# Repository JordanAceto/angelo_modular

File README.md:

## Custom 5u format modular synth with 12 modules

### Contains:
- VCO with 5-pulser waveshaper
- VCO with two sub-oscillators
- VCO with LFO range switch
- Voltage controlled wavefolder plus ring-modulator
- Voltage controlled filter with swapable filter-core plug-in boards
- Dual late MS20 style voltage controlled filter
- MIDI to CV plus audio input processor
- Dual 3-input DC coupled mixer
- Modulation source with voltage controlled LFO, sample-and-hold, and white noise source
- Dual Serge style slope generator
- Dual ADSR
- Dual VCA
- +/- 12 volt power supply

### User manuals can be found in the `/user_manuals/` directory. This directory also contains a document outlining any pcb kludges or changes to the current system.

### Documentation for the pcbs is in the `/pcb_docs/` directory

#### Documentation for each pcb consists of the following:
- A very brief README outlining the basics of the pcb

- `/construction_docs/` subdirectory which contains:
  - Gerbers for the circuit board
  - An interactive BOM which can be opened in a web browser
  - A pdf schematic

- `/kicad_docs/` subdirectory which contains the files needed to edit the schematic and pcb layout with kicad

- `/pics/` subdirectory which contains a few rendered pictures of the pcb for reference

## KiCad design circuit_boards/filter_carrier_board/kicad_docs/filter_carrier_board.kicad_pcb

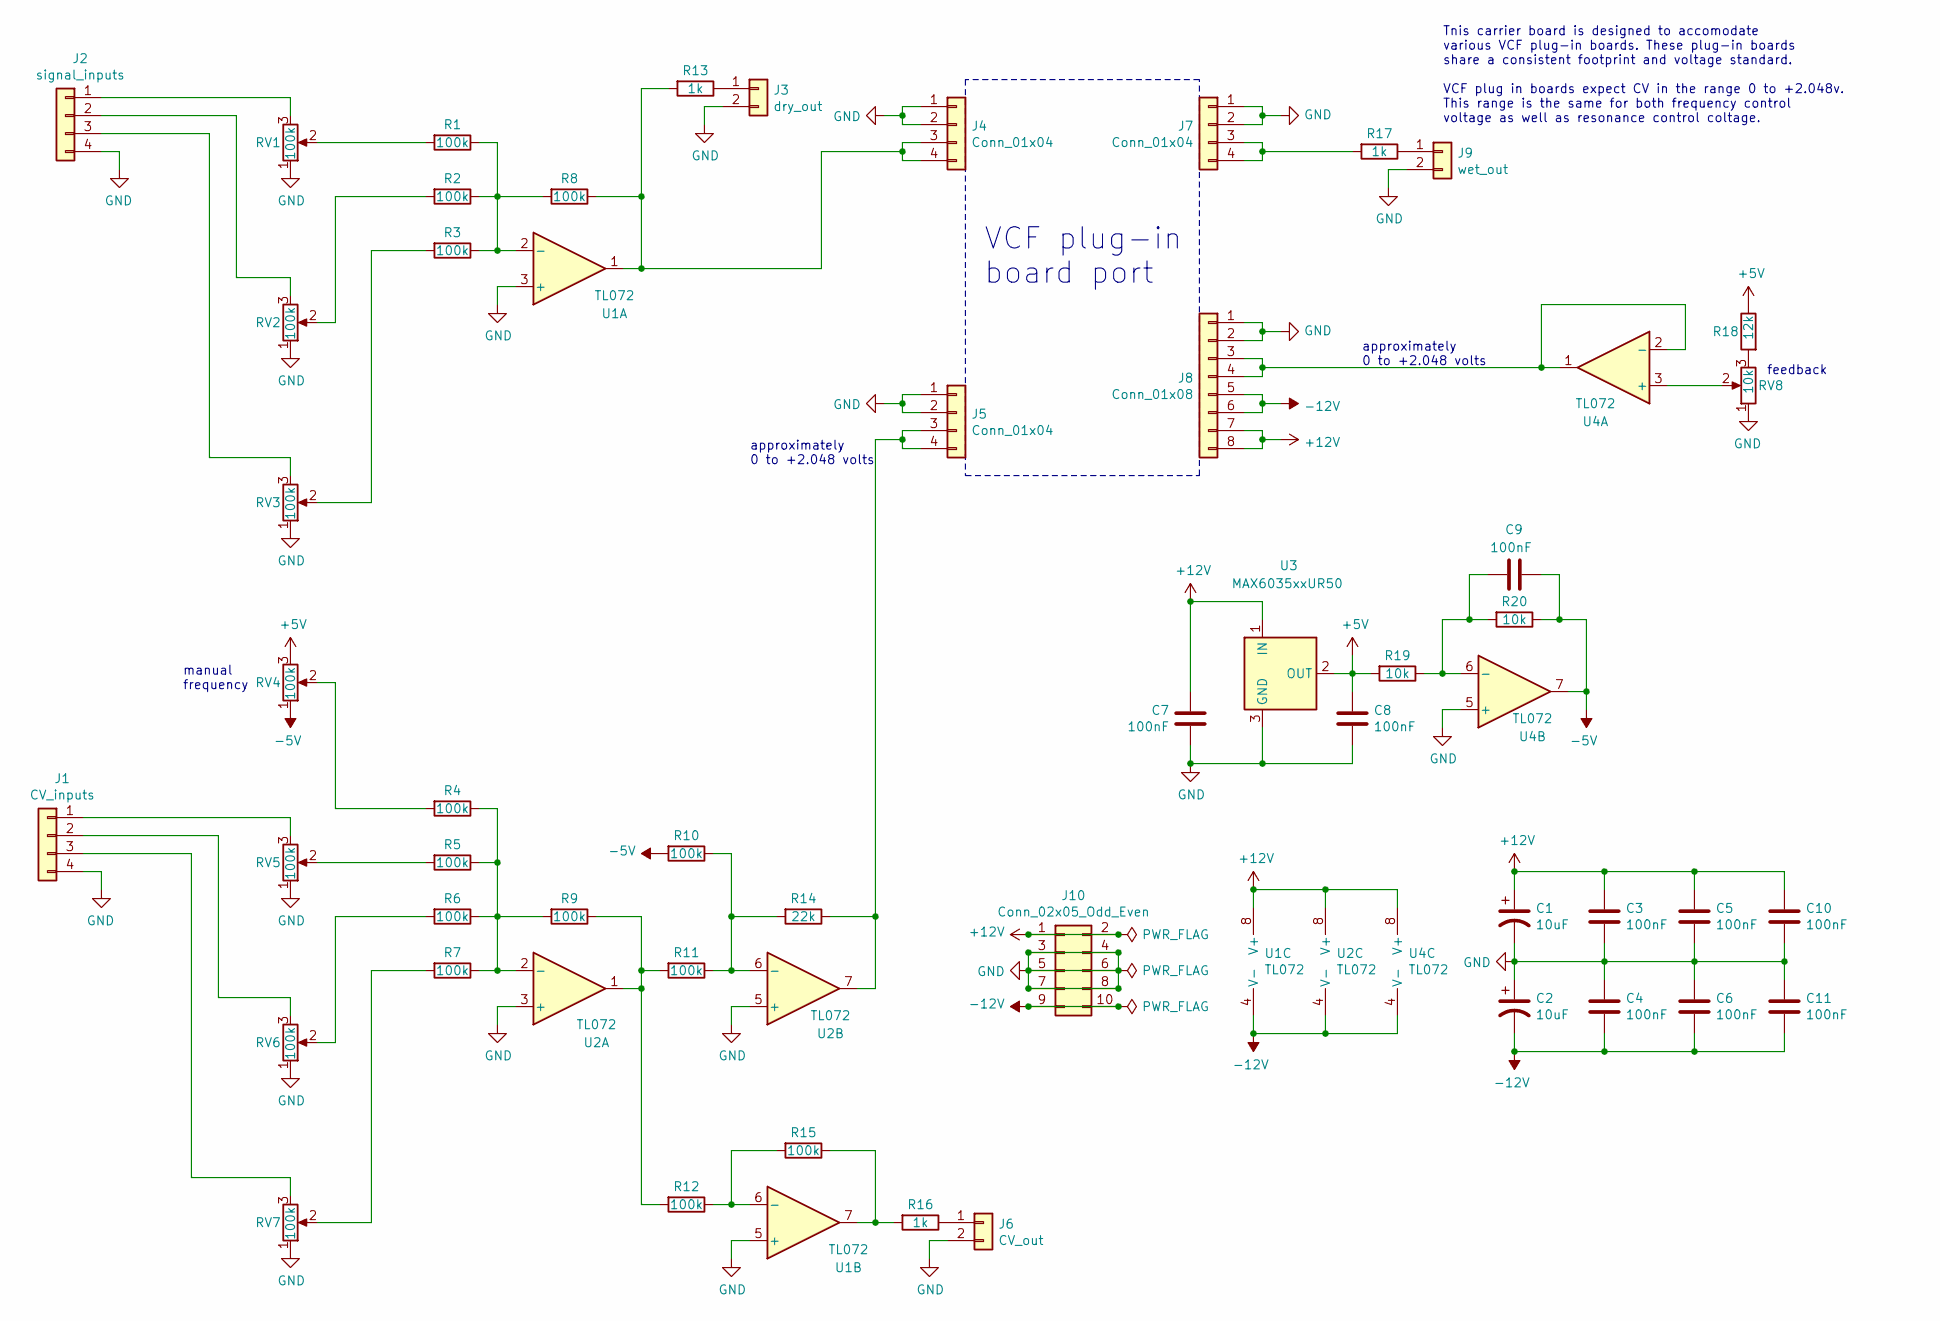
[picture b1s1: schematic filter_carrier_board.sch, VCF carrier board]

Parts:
C1, C2: 10uF; CP_Radial_D6.3mm_P2.50mm
C3, C4, C5, C6, C7, C8, C9, C10, C11: 100nF; C_Axial_L3.8mm_D2.6mm_P7.50mm_Horizontal
J1: CV_inputs; PinHeader_1x04_P2.54mm_Vertical
J2: signal_inputs; PinHeader_1x04_P2.54mm_Vertical
J3: dry_out; PinHeader_1x02_P2.54mm_Vertical
J4, J5, J7: Conn_01x04; PinSocket_1x04_P2.54mm_Vertical
J6: CV_out; PinHeader_1x02_P2.54mm_Vertical
J8: Conn_01x08; PinSocket_1x08_P2.54mm_Vertical
J9: wet_out; PinHeader_1x02_P2.54mm_Vertical
J10: Conn_02x05_Odd_Even; PinHeader_2x05_P2.54mm_Vertical
R1, R2, R3, R4, R5, R6, R7, R8, R9, R10, R11, R12, R15: 100k; R_Axial_DIN0207_L6.3mm_D2.5mm_P10.16mm_Horizontal
R13, R16, R17: 1k; R_Axial_DIN0207_L6.3mm_D2.5mm_P10.16mm_Horizontal
R14: 22k; R_Axial_DIN0207_L6.3mm_D2.5mm_P10.16mm_Horizontal
R18: 12k; R_Axial_DIN0207_L6.3mm_D2.5mm_P10.16mm_Horizontal
R19, R20: 10k; R_Axial_DIN0207_L6.3mm_D2.5mm_P10.16mm_Horizontal
RV1, RV2, RV3, RV4, RV5, RV6, RV7: 100k; Potentiometer_Alpha_RD901F-40-00D_Single_Vertical
RV8: 10k; Potentiometer_Alpha_RD901F-40-00D_Single_Vertical
U1, U2, U4: TL072; DIP-8_W7.62mm
U3: MAX6035xxUR50; SOT-23_Handsoldering

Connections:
+5V: C8.1, R18.1, R19.2, RV4.3, U3.2 (OUT)
+12V: C1.1, C3.1, C5.1, C7.1, C10.1, J8.7, J8.8, J10.1, J10.2, U1.8 (V+), U2.8 (V+), U3.1 (IN), U4.8 (V+)
-5V: C9.2, R10.2, R20.1, RV4.1, U4.7
-12V: C2.2, C4.2, C6.2, C11.2, J8.5, J8.6, J10.9, J10.10, U1.4 (V-), U2.4 (V-), U4.4 (V-)
GND: C1.2, C2.1, C3.2, C4.1, C5.2, C6.1, C7.2, C8.2, C10.2, C11.1, J1.4, J2.4, J3.2, J4.1, J4.2, J5.1, J5.2, J6.2, J7.1, J7.2, J8.1, J8.2, J9.2, J10.3, J10.4, J10.5, J10.6, J10.7, J10.8, RV1.1, RV2.1, RV3.1, RV5.1, RV6.1, RV7.1, RV8.1, U1.3 (+), U1.5 (+), U2.3 (+), U2.5 (+), U3.3 (GND), U4.5 (+)
unnamed: C9.1, R19.1, R20.2, U4.6 (-)
unnamed: J1.1, RV5.3
unnamed: J1.2, RV6.3
unnamed: J1.3, RV7.3
unnamed: J2.1, RV1.3
unnamed: J2.2, RV2.3
unnamed: J2.3, RV3.3
unnamed: J3.1, R13.1
unnamed: J4.3, J4.4, R8.1, R13.2, U1.1
unnamed: J5.3, J5.4, R14.1, U2.7
unnamed: J6.1, R16.1
unnamed: J7.3, J7.4, R17.2
unnamed: J8.3, J8.4, U4.1, U4.2 (-)
unnamed: J9.1, R17.1
unnamed: R1.1, R2.1, R3.1, R8.2, U1.2 (-)
unnamed: R1.2, RV1.2
unnamed: R2.2, RV2.2
unnamed: R3.2, RV3.2
unnamed: R4.1, R5.1, R6.1, R7.1, R9.2, U2.2 (-)
unnamed: R4.2, RV4.2
unnamed: R5.2, RV5.2
unnamed: R6.2, RV6.2
unnamed: R7.2, RV7.2
unnamed: R10.1, R11.1, R14.2, U2.6 (-)
unnamed: R9.1, R11.2, R12.2, U2.1
unnamed: R12.1, R15.2, U1.6 (-)
unnamed: R15.1, R16.2, U1.7
unnamed: R18.2, RV8.3
unnamed: RV8.2, U4.3 (+)

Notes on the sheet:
manual frequency
Tnis carrier board is designed to accomodate various VCF plug-in boards. These plug-in boards share a consistent footprint and voltage standard. VCF plug in boards expect CV in the range 0 to +2.048v. This range is the same for both frequency control voltage as well as resonance control coltage.
approximately 0 to +2.048 volts
VCF plug-in board port
feedback

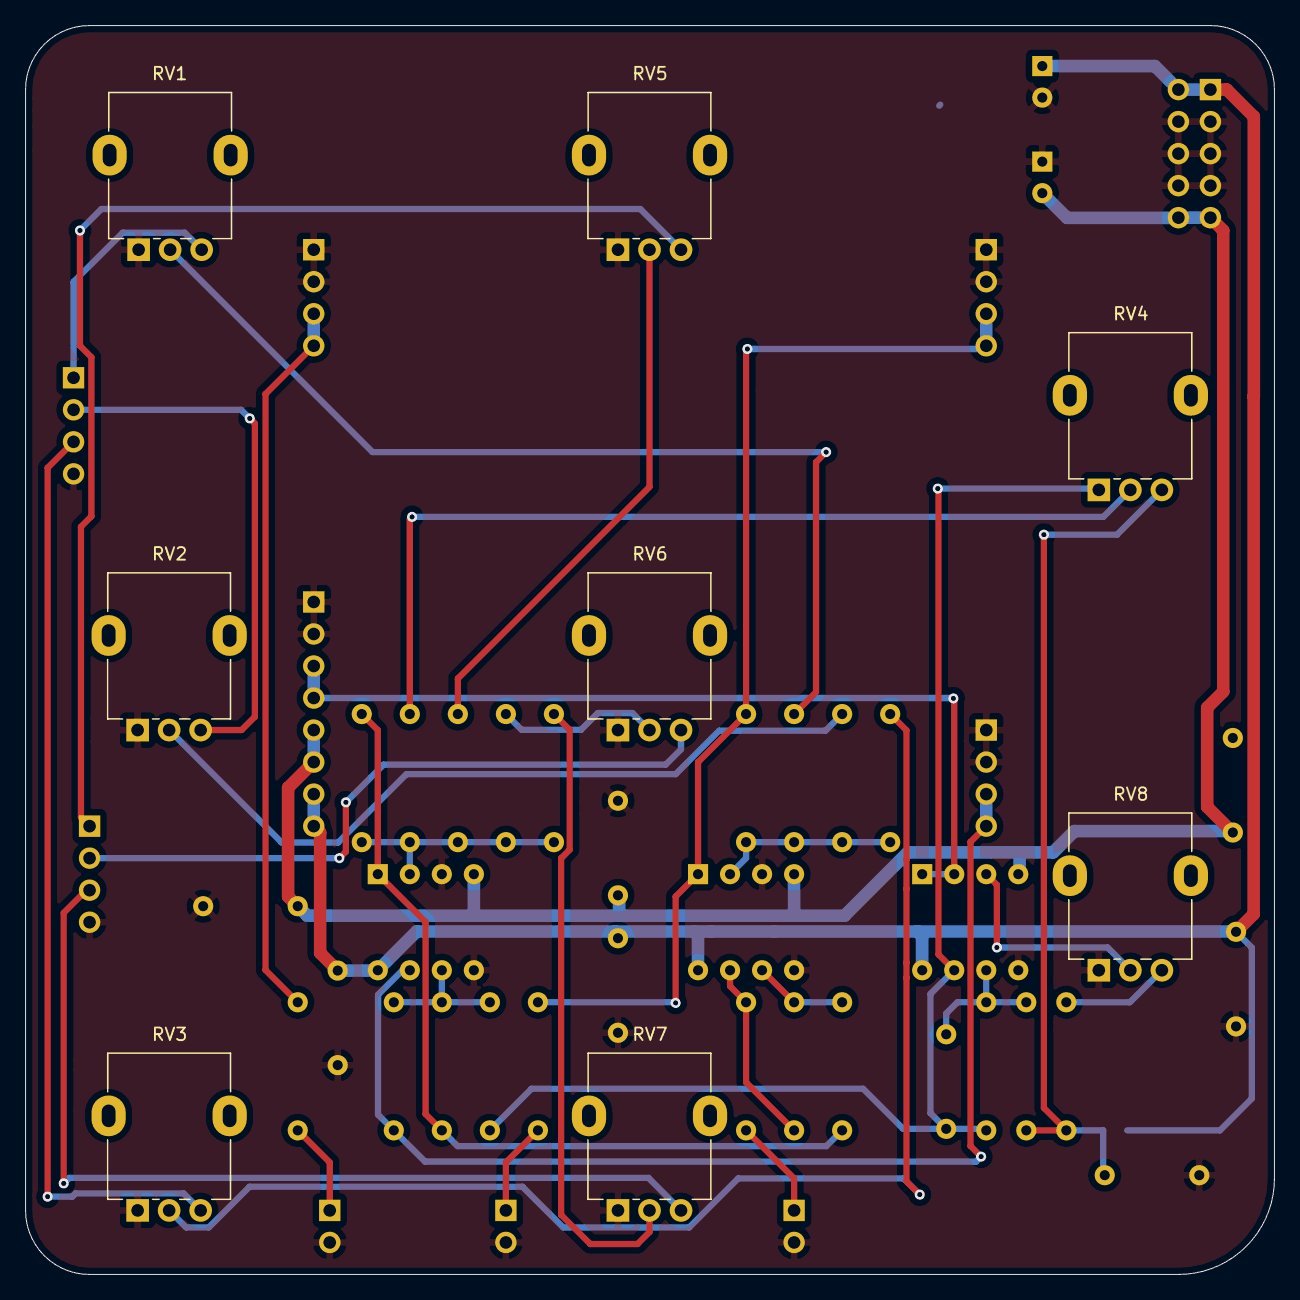
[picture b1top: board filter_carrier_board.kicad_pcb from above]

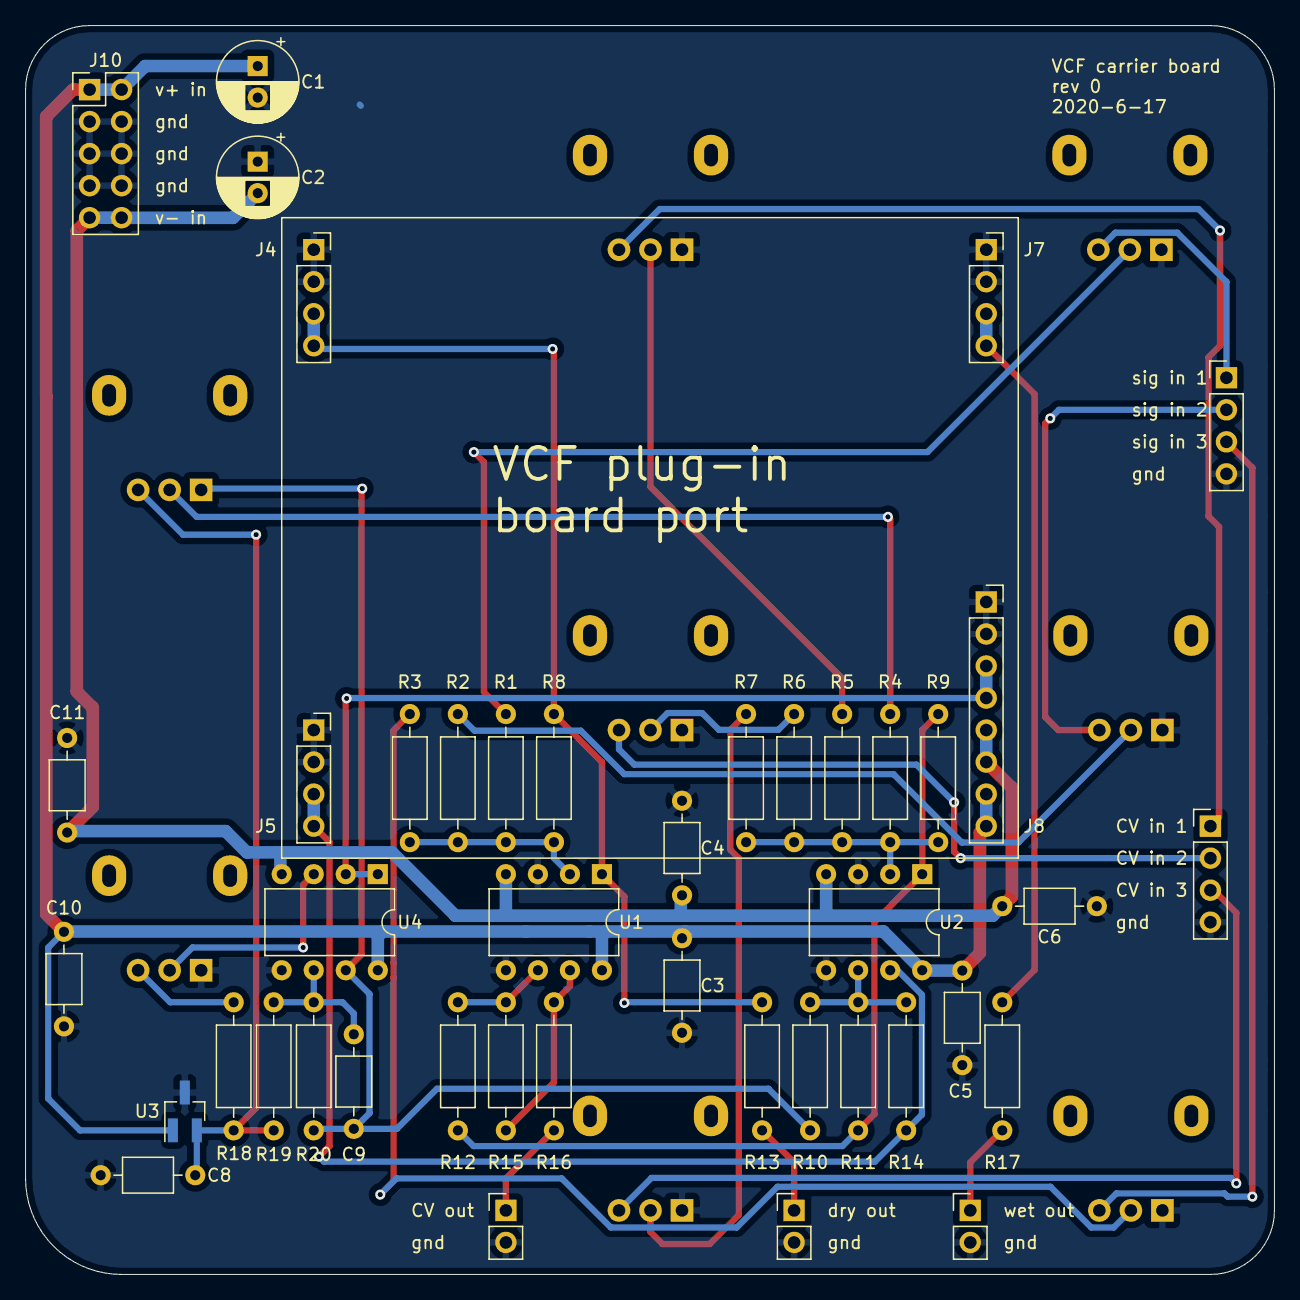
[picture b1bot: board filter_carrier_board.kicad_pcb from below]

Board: 2 copper layers, 99.1 x 99.1 mm, 52 parts (44 on the bottom side), 34 nets.

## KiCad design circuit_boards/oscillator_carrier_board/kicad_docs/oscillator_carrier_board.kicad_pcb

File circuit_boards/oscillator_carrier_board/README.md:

# VCO carrier board

Motherboard pcb for oscillators. Contains a port for a VCO core and a port for auxilliary waveshapers, and an octave switch.

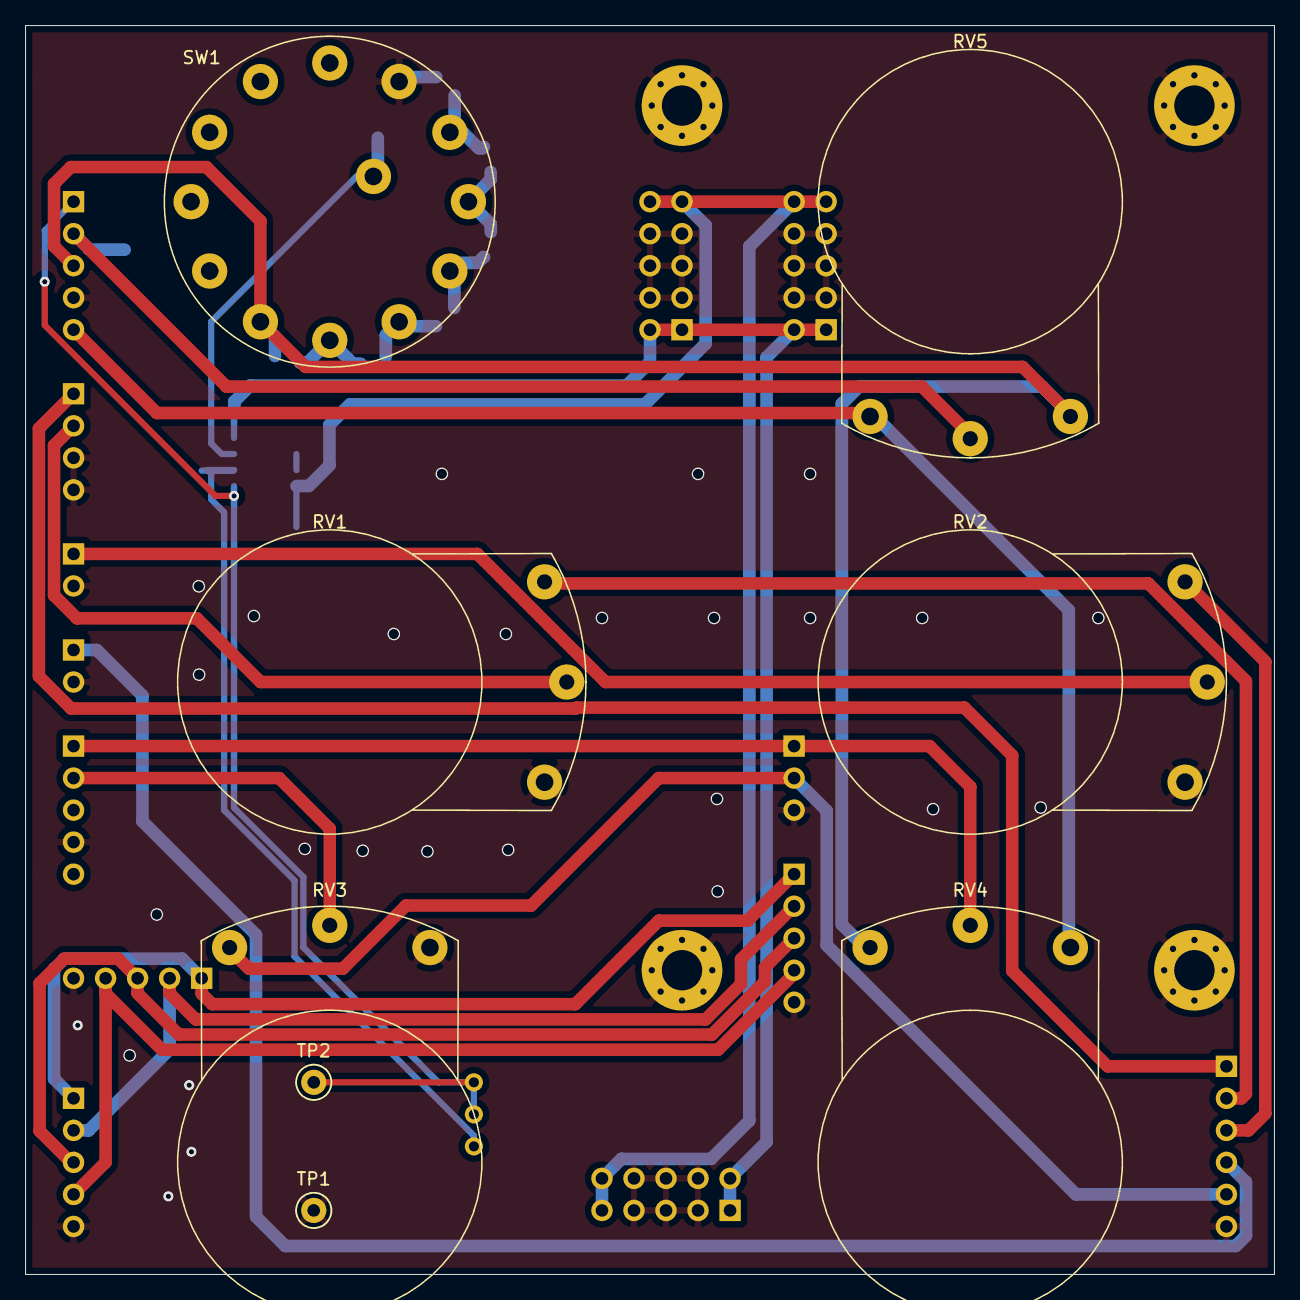
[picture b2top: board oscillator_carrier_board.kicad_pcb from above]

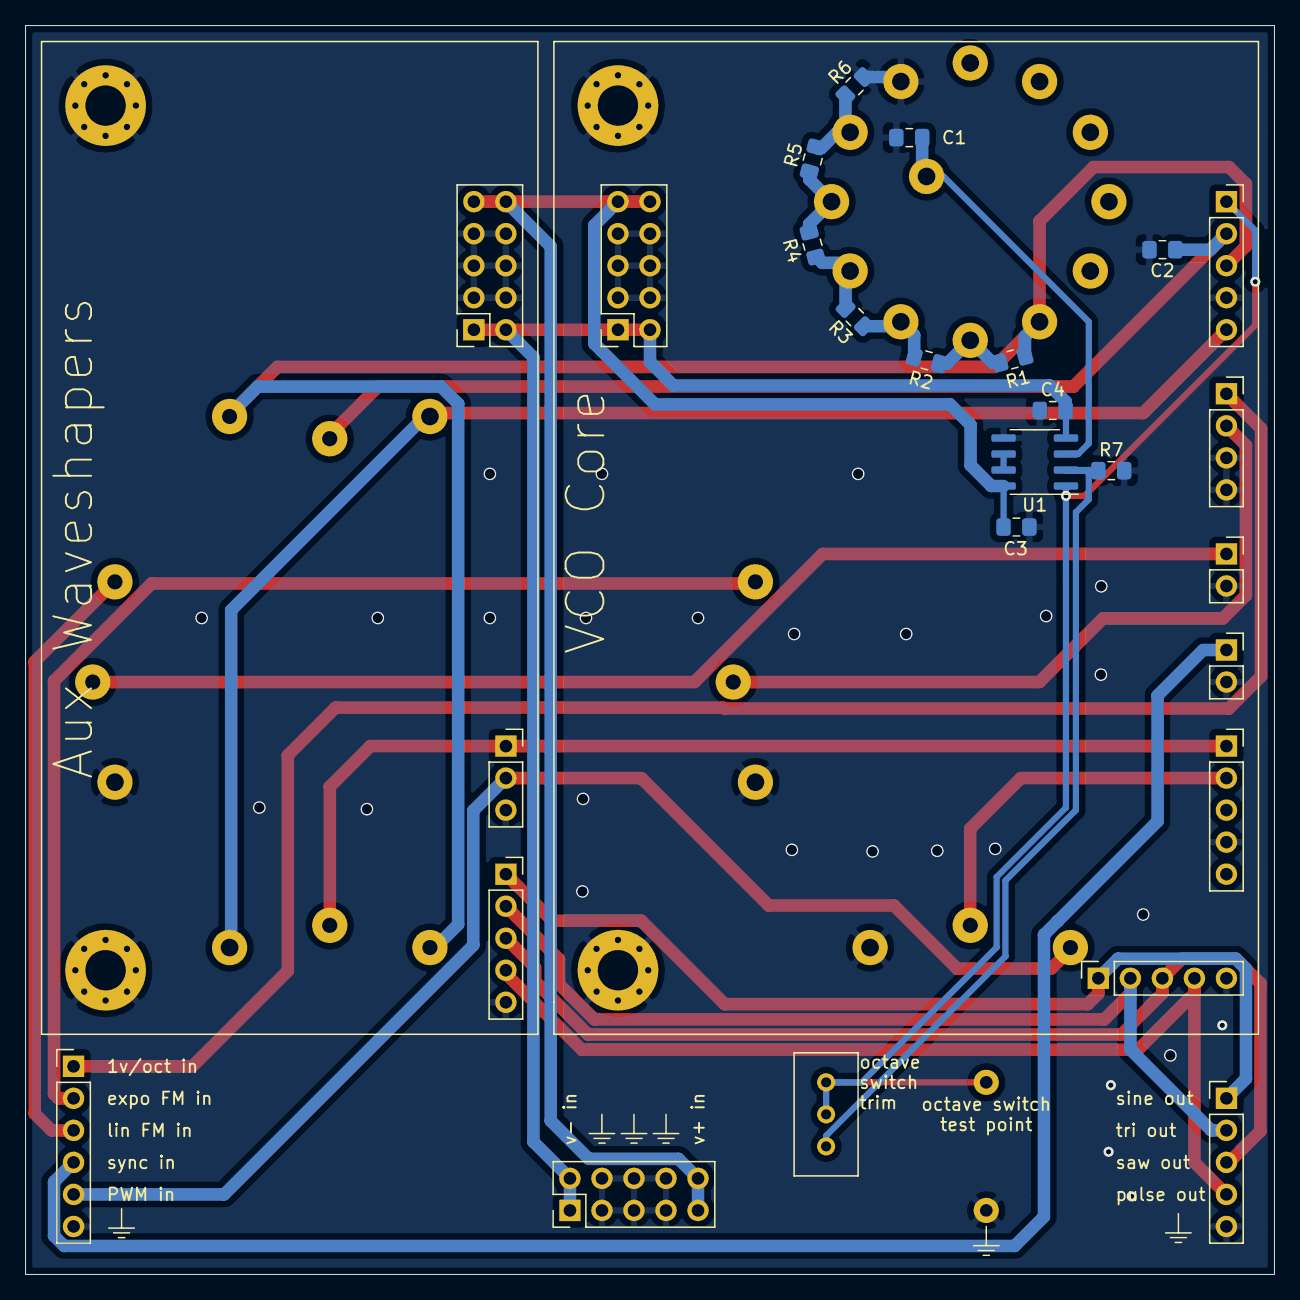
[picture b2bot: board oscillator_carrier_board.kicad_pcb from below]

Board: 2 copper layers, 99.1 x 99.1 mm, 38 parts (26 on the bottom side), 28 nets.

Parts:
C1, C2, C3, C4: 100nF; C_0805_2012Metric_Pad1.15x1.40mm_HandSolder
H1, H2, H3, H4: MountingHole_Pad; MountingHole_3.2mm_M3_Pad_Via
J1: Conn_01x06; PinHeader_1x06_P2.54mm_Vertical
J2: Conn_01x05; PinHeader_1x05_P2.54mm_Vertical
J3: power_header; PinHeader_2x05_P2.54mm_Vertical
J4: Conn_01x04; PinSocket_1x04_P2.54mm_Vertical
J5, J6: Conn_01x02; PinSocket_1x02_P2.54mm_Vertical
J7, J10, J11: Conn_01x05; PinSocket_1x05_P2.54mm_Vertical
J8, J13: power_header; PinSocket_2x05_P2.54mm_Vertical
J9: to_VCO_board; PinSocket_1x05_P2.54mm_Vertical
J12: Conn_01x03; PinSocket_1x03_P2.54mm_Vertical
R1, R2, R3, R4, R5, R6: 1k; R_0805_2012Metric_Pad1.15x1.40mm_HandSolder
R7: 68k; R_0805_2012Metric_Pad1.15x1.40mm_HandSolder
RV1, RV2, RV3, RV4, RV5: 100k; alpha_RV24AF-40
RV6: 50k; Potentiometer_Bourns_3296W_Vertical
SW1: octave_switch; apha_SR2612F-0112
TP1, TP2: TestPoint; TestPoint_Keystone_5000-5004_Miniature
U1: TL072; SOIC-8_3.9x4.9mm_P1.27mm

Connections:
+5V: J7.3, J10.3, R1.2, RV4.3, RV5.3, SW1.7
+12V: C3.1, J3.9, J3.10, J8.9, J8.10, J13.9, J13.10, U1.8
-5V: J7.5, J10.5, RV4.1, RV5.1
-12V: C4.2, J3.1, J3.2, J8.1, J8.2, J13.1, J13.2, U1.4
/VCO_core_components/1v_oct_in: J1.1, J4.1
/VCO_core_components/PWM_in: J1.5, J12.2, RV3.3
/VCO_core_components/expo_FM_in: J1.2, RV1.3
/VCO_core_components/lin_FM_in: J1.3, RV2.3
/VCO_core_components/sync_in: J1.4, J6.1
/aux_waveshaper_components/man_pulse_in: J7.1, J12.1, RV4.2
/aux_waveshaper_components/pulse_in: J2.4, J9.4, J11.4
/aux_waveshaper_components/saw_in: J2.3, J9.3, J11.3
/aux_waveshaper_components/sine_in: J2.1, J9.1, J11.1
/aux_waveshaper_components/tri_in: J2.2, J9.2, J11.2
GND: C1.2, C2.2, C3.2, C4.1, H1.1, H2.1, H3.1, H4.1, J1.6, J2.5, J3.3, J3.4, J3.5, J3.6, J3.7, J3.8, J4.3, J4.4, J5.2, J6.2, J7.4, J8.3, J8.4, J8.5, J8.6, J8.7, J8.8, J9.5, J10.4, J11.5, J12.3, J13.3, J13.4, J13.5, J13.6, J13.7, J13.8, R6.1, R7.2, RV1.1, RV2.1, RV3.1, SW1.1, TP1.1, U1.5
unnamed: C1.1, SW1.13, U1.3
unnamed: C2.1, J10.2, RV5.2
unnamed: J4.2, RV1.2
unnamed: J5.1, RV2.2
unnamed: J7.2, RV3.2
unnamed: J10.1, RV6.2, RV6.3, TP2.1, U1.1
unnamed: R1.1, R2.2, SW1.6
unnamed: R2.1, R3.2, SW1.5
unnamed: R3.1, R4.2, SW1.4
unnamed: R4.1, R5.2, SW1.3
unnamed: R5.1, R6.2, SW1.2
unnamed: R7.1, RV6.1, U1.2
unnamed: U1.6, U1.7

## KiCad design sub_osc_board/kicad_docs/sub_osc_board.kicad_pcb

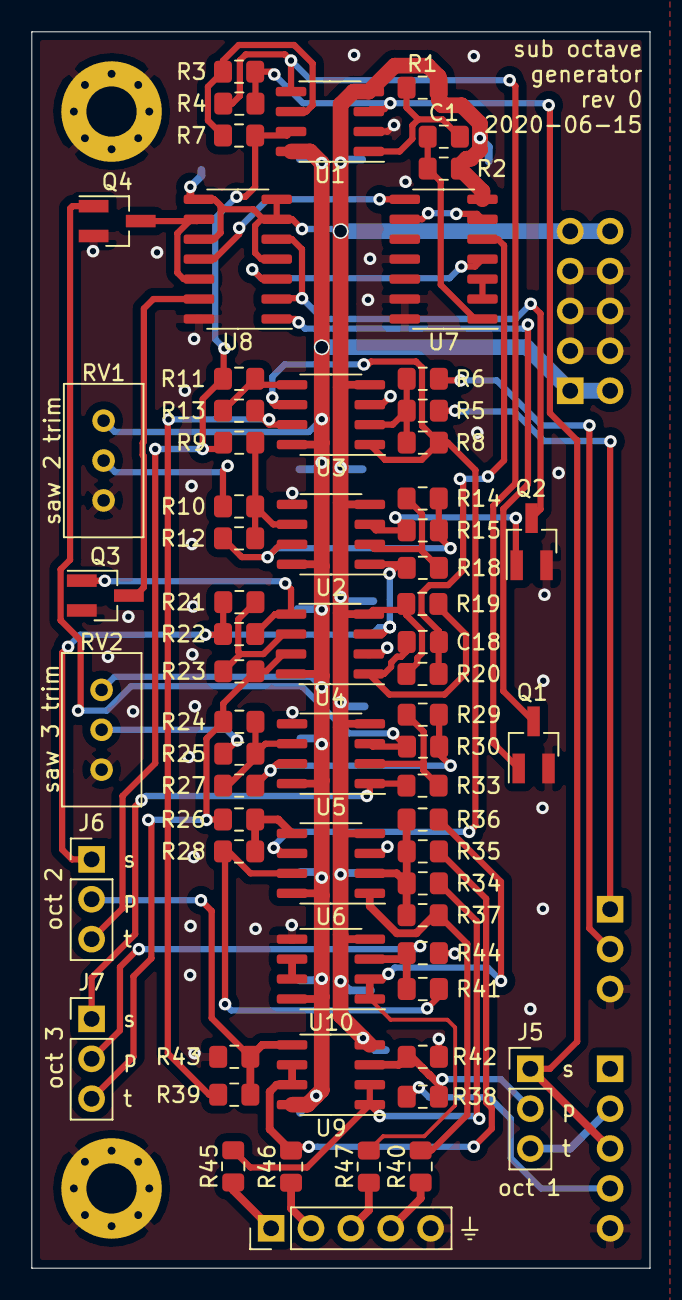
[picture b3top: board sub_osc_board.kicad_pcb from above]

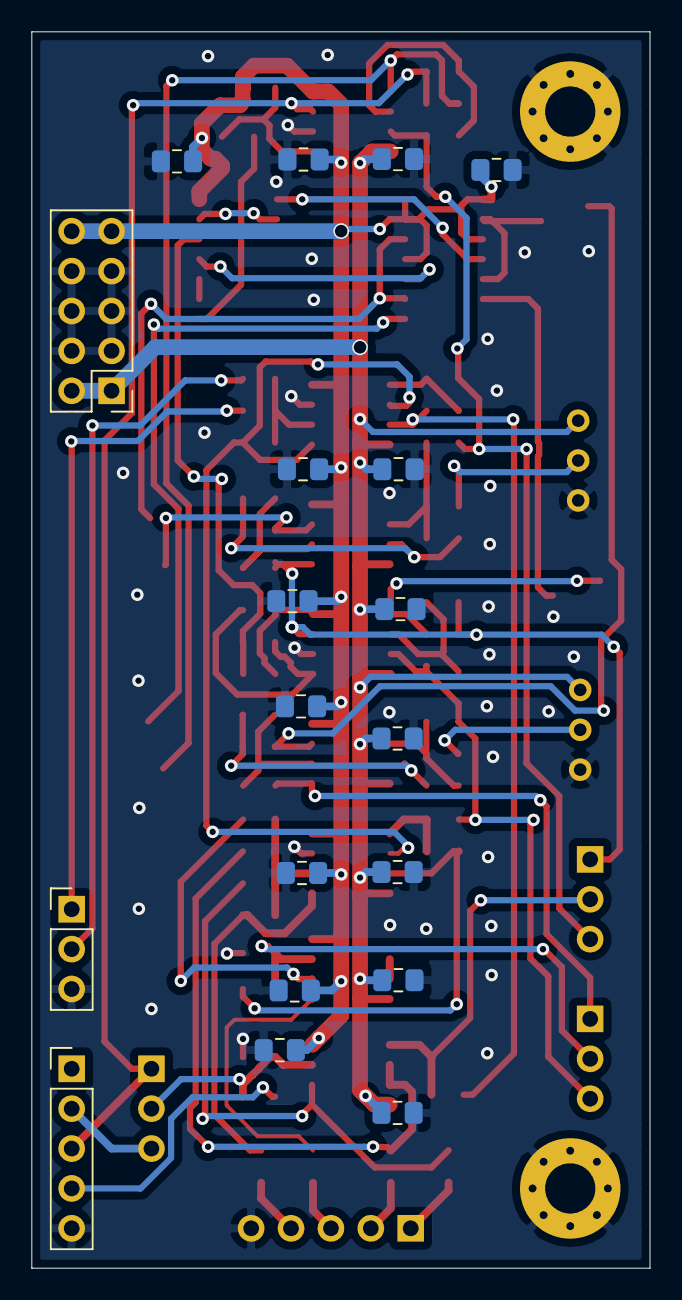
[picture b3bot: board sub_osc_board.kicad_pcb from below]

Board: 2 copper layers, 39.4 x 78.7 mm, 86 parts (19 on the bottom side), 57 nets.

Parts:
C1, C18: 1nF; C_0805_2012Metric_Pad1.15x1.40mm_HandSolder
C2, C3, C4, C5, C6, C7, C8, C9, C10, C11, C12, C13, C14, C15: 100nF; C_0805_2012Metric_Pad1.15x1.40mm_HandSolder
C16, C17: 10uF; C_0805_2012Metric_Pad1.15x1.40mm_HandSolder
H1, H2: MountingHole_Pad; MountingHole_3.2mm_M3_Pad_Via
J1: signal_inputs; PinHeader_1x05_P2.54mm_Vertical
J2: pwm_inputs; PinHeader_1x03_P2.54mm_Vertical
J3: power_input; PinHeader_2x05_P2.54mm_Vertical
J4: signal_outputs; PinHeader_1x05_P2.54mm_Vertical
J5, J6, J7: Conn_01x03; PinHeader_1x03_P2.54mm_Vertical
Q1, Q2, Q3, Q4: MMBF5457; SOT-23_Handsoldering
R1, R19: 10k; R_0805_2012Metric_Pad1.15x1.40mm_HandSolder
R2, R20: 22k; R_0805_2012Metric_Pad1.15x1.40mm_HandSolder
R3, R4, R6, R7, R8, R9, R10, R14, R15, R18, R21, R22, R23, R24, R25, R29, R30, R33, R34, R35, R36, R43, R44: 100k; R_0805_2012Metric_Pad1.15x1.40mm_HandSolder
R5: 110k; R_0805_2012Metric_Pad1.15x1.40mm_HandSolder
R11, R26: 2k2; R_0805_2012Metric_Pad1.15x1.40mm_HandSolder
R12, R27: 51k; R_0805_2012Metric_Pad1.15x1.40mm_HandSolder
R13, R28: 2M2; R_0805_2012Metric_Pad1.15x1.40mm_HandSolder
R37: 33k; R_0805_2012Metric_Pad1.15x1.40mm_HandSolder
R38, R39, R41: 120k; R_0805_2012Metric_Pad1.15x1.40mm_HandSolder
R40, R45, R46, R47: 1k; R_0805_2012Metric_Pad1.15x1.40mm_HandSolder
R42: dnf; R_0805_2012Metric_Pad1.15x1.40mm_HandSolder
RV1, RV2: 100k; Potentiometer_Bourns_3296W_Vertical
U1, U2, U3, U4, U5, U6, U9, U10: TL072; SOIC-8_3.9x4.9mm_P1.27mm
U7: 40106; SOIC-14_3.9x8.7mm_P1.27mm
U8: 4013; SOIC-14_3.9x8.7mm_P1.27mm

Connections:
+12V: C4.1, C6.1, C8.1, C10.1, C12.1, C14.1, C16.1, J3.1, J3.2, RV1.1, RV2.1, U1.8, U2.8, U3.8, U4.8, U5.8, U6.8, U9.8, U10.8
-12V: C2.2, C3.2, C5.2, C7.2, C9.2, C11.2, C13.2, C15.2, C17.2, J3.9, J3.10, R1.2, R2.2, R19.2, R20.2, U1.4, U2.4, U3.4, U4.4, U5.4, U6.4, U7.7, U8.4, U8.6, U8.7, U8.8, U8.10, U9.4, U10.4
/base_oct_out: R34.2, R45.2, U9.1, U9.2
/mix_out: R37.1, R40.2, U6.1
/pulse_in: J1.4, R38.2
/pulse_over_2: R13.1, R39.2, U3.7
/pulse_over_4: R28.1, R41.2, U6.7
/saw_in: J1.3, J5.1, R3.2, R4.2, U1.3
/saw_over_2: J6.1, R18.1, R21.2, R22.2, U2.1, U4.3
/saw_over_4: J7.1, R33.1, U5.1
/sub_oct_1_out: R35.2, R46.2, U9.6, U9.7
/sub_oct_2_out: R36.2, R47.2, U10.1, U10.2
/sub_osc_1/man_pw_in_1: J2.1, R5.2
/sub_osc_1/pwm_in_1: J2.2, R6.2
/sub_osc_1/summed_PWM: R8.1, U3.1, U3.6, U6.6
/tri_in: J1.2, J5.3
/tri_over_2: J6.3, R7.1, R9.2, R11.2, U1.7
/tri_over_4: J7.3, R23.1, R24.2, R26.2, U4.7
GND: C2.1, C3.1, C4.2, C5.1, C6.2, C7.1, C8.2, C9.1, C10.2, C11.1, C12.2, C13.1, C14.2, C15.1, C16.2, C17.1, H1.1, H2.1, J1.5, J2.3, J3.3, J3.4, J3.5, J3.6, J3.7, J3.8, J4.5, Q1.2, Q2.2, Q3.2, Q4.2, R42.2, R43.2, R44.2, RV1.3, RV2.3, U1.2, U2.5, U3.3, U4.2, U5.5, U6.3, U7.11, U7.13, U7.14, U8.14, U10.5
unnamed: C1.1, R2.1, U7.1
unnamed: C1.2, R1.1, U1.1
unnamed: C18.1, R20.1, U7.5
unnamed: C18.2, R19.1, U4.1
unnamed: J4.1, R45.1
unnamed: J4.2, R46.1
unnamed: J4.3, R47.1
unnamed: J4.4, R40.1
unnamed: J5.2, R38.1, R42.1, U9.3
unnamed: J6.2, R39.1, R43.1, U9.5
unnamed: J7.2, R41.1, R44.1, U10.3
unnamed: Q1.1, R4.1, U1.5
unnamed: Q1.3, U8.1
unnamed: Q2.1, R15.1, U2.3
unnamed: Q2.3, U8.2, U8.5
unnamed: Q3.1, R22.1, U4.5
unnamed: Q3.3, U8.13
unnamed: Q4.1, R30.1, U5.3
unnamed: Q4.3, U8.9, U8.12
unnamed: R3.1, R7.2, U1.6
unnamed: R5.1, R6.1, R8.2, U3.2
unnamed: R9.1, R10.1, R12.2, U2.6
unnamed: R10.2, RV1.2
unnamed: R11.1, R13.2, U3.5
unnamed: R12.1, R14.2, R15.2, U2.7
unnamed: R14.1, R18.2, U2.2
unnamed: R21.1, R23.2, U4.6
unnamed: R24.1, R25.1, R27.2, U5.6
unnamed: R25.2, RV2.2
unnamed: R26.1, R28.2, U6.5
unnamed: R27.1, R29.2, R30.2, U5.7
unnamed: R29.1, R33.2, U5.2
unnamed: R34.1, R35.1, R36.1, R37.2, U6.2
unnamed: U7.2, U7.3
unnamed: U7.4, U8.3
unnamed: U7.6, U7.9
unnamed: U7.8, U8.11
unnamed: U10.6, U10.7

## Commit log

2020-06-17 edit readme
2020-06-19 slope gen progress, misc cleanup
2020-06-19 fix resistor on wrong side of pcb
2020-06-19 add CEM3340 lpf plug-in board
2020-06-19 add note about mode resistor
2020-06-19 add no-connects to MS20 VCF schematic
2020-06-19 add +/- 5 volt ref to VCF carrier board
2020-06-21 make gerbers of most boards, add unfinished modulation source
2020-06-21 add unfinished dual ADSR
2020-06-21 rearrange dual adsr dir
2020-06-21 generate mod source gerbers
2020-06-21 generate adsr gerbers
2020-06-22 change modulation-source fm circuit, make new gerbers
2020-06-22 generate more gerbers
2020-06-23 add component values to ADSR LPFs
2020-06-25 try out interactive BOM plugin
2020-06-26 add values to pcb, regenerate BOM
2020-06-26 generate BOMs for most boards
2020-06-26 add gitignore for unnecessary kicad files
2020-06-26 fill in VCO r values, generate BOM
2020-06-26 add some missing resistor values
2020-07-01 fix pcb error, change some values
2020-07-01 mess around with 2164 lpf
2020-07-01 update pcb and BOM with correct values
2020-07-05 scale pwm circuit and add power flags
2020-07-05 change FETs and cap values
2020-07-06 update values to scale frequency and noise level
2020-07-06 change value to do-not-fit
2020-07-06 apply componet change to pcb
2020-07-06 big directory change, update readme
2020-07-15 add cubeide project firmware for dual ADSR
2020-07-15 add panel layouts
2020-07-15 fix mistake on suboctave VCO panel layout
2020-07-16 remove 2164 LPF board, may add it back in when it is complete
2020-07-17 change CEM3320 VCF BOM to new interactive stlye
2020-07-17 add CEM3320 VCF gerbers
2020-07-17 change phasor BOM to new interactive style
2020-07-17 add optical phasor gerbers
2020-07-17 add rendered pics of wavefolder pcb
2020-07-17 add rendered pics of several pcbs
2020-07-20 small changes to wave folder CV bias and output level
2020-07-21 change scaling resistors for manual cutoff controls
2020-07-21 fill in values for octave switch, add VCO carrier BOM
2020-07-21 embiggen 5-pulser manual PW resistor
2020-07-22 generate VCA schematic
2020-07-22 add ms20 title block, generate ms20 schemo
2020-07-22 add mod source title and schematic
2020-07-22 add 5-pulser title and schematic
2020-07-22 add title
2020-07-22 add several titles and schematics
2020-07-23 change sub-osc PWM range and mixer gain
2020-07-23 move licenses to top level
2020-07-23 update stm32 breakout readme
2020-07-23 add pics and readme
2020-07-23 remove outdated BOM infro from readme
2020-07-23 add readme
2020-07-23 add pics and reame
2020-07-23 add top-level ADSR module readme
2020-07-23 add some user manuals
2020-07-23 put all pcb docs in circuit_boards directory
2020-07-24 add mixer manual
2020-07-24 change cap so noise biases quicker
2020-07-25 add schematic, fix BOM typo
2020-07-25 add title block, generate schematic
2020-07-25 add title block and schematic
2020-07-25 add pcb_kludges document to user manuals
2020-07-25 add VCO manuals
2020-07-25 add midi-CV/audio input manual
2020-07-25 remove panel layouts
2020-07-25 rename pcb_docs directory
2020-07-25 edit readme phrasing
2020-07-28 fix some ADSR code problems
2020-07-29 add note about ring-mod kludges
2020-07-31 add some pictures
2020-07-31 add pic to readme
2020-08-06 increase decay and release times
2020-08-13 update CEM3320 VCF

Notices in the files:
circuit_boards/filter_carrier_board/kicad_docs/filter_carrier_board.kicad_pcb:
License: CC by 4.0
circuit_boards/filter_carrier_board/kicad_docs/filter_carrier_board.sch:
creativecommons.org/licenses/by/4.0
